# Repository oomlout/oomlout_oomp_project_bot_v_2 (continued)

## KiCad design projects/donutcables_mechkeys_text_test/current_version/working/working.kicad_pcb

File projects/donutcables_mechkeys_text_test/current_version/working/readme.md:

# mechkeys
 
## summary 
* id: donutcables_mechkeys_text_test
* user: donutcables
* name: mechkeys
* board: text_test
* repo: https://github.com/DonutCables/mechkeys
* src_file_repo_kicad_pcb: text-test-project/text-test.kicad_pcb
* src_file_repo_kicad_pcb_link: https://github.com/DonutCables/mechkeys/tree/master/text-test-project/text-test.kicad_pcb

* src_file_repo_sch: text-test-project/text-test.sch
* src_file_repo_sch_link: https://github.com/DonutCables/mechkeys/tree/master/text-test-project/text-test.sch
* full details link: https://github.com/oomlout/oomlout_oomp_project_bot_v_2/tree/main/projects/donutcables_mechkeys_text_test/current_version/working

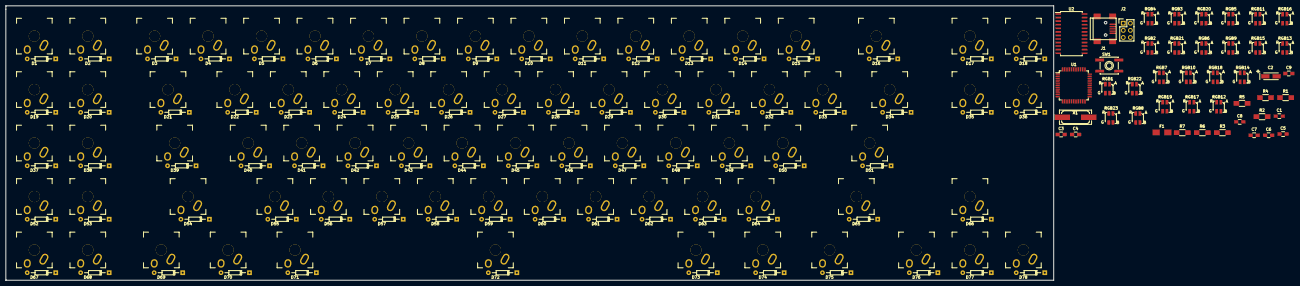
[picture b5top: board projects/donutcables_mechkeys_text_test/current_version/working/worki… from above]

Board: 2 copper layers, 373.4 x 97.8 mm, 202 parts (0 on the bottom side), 133 nets, no tracks yet.

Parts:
C1: C; C_0805_HandSoldering
C2: 10µF; TantalC_SizeA_EIA-3216_HandSoldering
C3, C4, C5, C9: 0.1µF; C_0805_HandSoldering
C6, C7: 18pF; C_0805_HandSoldering
C8: 1µF; C_0805_HandSoldering
D1, D2, D3, D4, D5, D6, D7, D8, D9, D10, D11, D12, D13, D14, D15, D16, D17, D18, D19, D20, D21, D22, D23, D24, D25, D26, D27, D28, D29, D30, D31, D32, D33, D34, D35, D36, D37, D38, D39, D40, D41, D42, D43, D44, D45, D46, D47, D48, D49, D50, D51, D52, D53, D54, D55, D56, D57, D58, D59, D60, D61, D62, D63, D64, D65, D66, D67, D68, D69, D70, D71, D72, D73, D74, D75, D76, D77, D78: D; Diode_DO-35_SOD27_Horizontal_RM10
F1: FP_Small; Fuse_SMD1206_HandSoldering
J1: USB_OTG; USB_Mini-B
J2: PRG; Pin_Header_Straight_2x03
R1: R; R_1206_HandSoldering
R2: R2; R_1206_HandSoldering
R3: R3; R_1206_HandSoldering
R4: R4; R_1206_HandSoldering
R5, R6: 22; R_1206_HandSoldering
R7: 10k; R_1206_HandSoldering
RGB1, RGB2, RGB3, RGB4, RGB5, RGB6, RGB7, RGB8, RGB9, RGB10, RGB11, RGB12, RGB13, RGB14, RGB15, RGB16, RGB17, RGB18, RGB19, RGB20, RGB21, RGB22, RGB23: Led_RGB_CA; SMP4-RGB
SW1: SW_RST; SW_SPST_EVQP0
SW_A_40: MX_LED; MXALPS-NOLED
SW_Alt_71, SW_Alt_73: MX_LED; MXALPS-NOLED
SW_B_59: MX_LED; MXALPS-NOLED
SW_Backspace_16: MX_LED; MXALPS-NOLED
SW_C_57: MX_LED; MXALPS-NOLED
SW_Caps_39: MX_LED; MXALPS-NOLED
SW_Ctrl_69: MX_LED; MXALPS-NOLED
SW_D_42: MX_LED; MXALPS-NOLED
SW_Del_35: MX_LED; MXALPS-NOLED
SW_E_24: MX_LED; MXALPS-NOLED
SW_Enter_51: MX_LED; MXALPS-NOLED
SW_F1_1, SW_F2_2, SW_F3_19, SW_F4_20, SW_F5_37, SW_F6_38, SW_F7_52, SW_F8_53, SW_F9_67, SW_F10_68: MX_LED; MXALPS-NOLED
SW_F_43: MX_LED; MXALPS-NOLED
SW_G_44: MX_LED; MXALPS-NOLED
SW_H_45: MX_LED; MXALPS-NOLED
SW_I_29: MX_LED; MXALPS-NOLED
SW_Ins_17: MX_LED; MXALPS-NOLED
SW_J_46: MX_LED; MXALPS-NOLED
SW_K_47: MX_LED; MXALPS-NOLED
SW_L_48: MX_LED; MXALPS-NOLED
SW_M_61: MX_LED; MXALPS-NOLED
SW_Menu_75: MX_LED; MXALPS-NOLED
SW_N_60: MX_LED; MXALPS-NOLED
SW_O_30: MX_LED; MXALPS-NOLED
SW_P_31: MX_LED; MXALPS-NOLED
SW_PgDn_36: MX_LED; MXALPS-NOLED
SW_PgUp_18: MX_LED; MXALPS-NOLED
SW_Q_22: MX_LED; MXALPS-NOLED
SW_R_25: MX_LED; MXALPS-NOLED
SW_S_41: MX_LED; MXALPS-NOLED
SW_Shift_54, SW_Shift_65: MX_LED; MXALPS-NOLED
SW_T_26: MX_LED; MXALPS-NOLED
SW_Tab_21: MX_LED; MXALPS-NOLED
SW_U_28: MX_LED; MXALPS-NOLED
SW_V_58: MX_LED; MXALPS-NOLED
SW_W_23: MX_LED; MXALPS-NOLED
SW_Win_70, SW_Win_74: MX_LED; MXALPS-NOLED
SW_X4Y1_3, SW_X5Y1_4, SW_X6Y1_5, SW_X7Y1_6, SW_X8Y1_7, SW_X8Y5_72, SW_X9Y1_8, SW_X10Y1_9, SW_X11Y1_10, SW_X12Y1_11, SW_X13Y1_12, SW_X13Y4_62, SW_X14Y1_13, SW_X14Y4_63, SW_X15Y1_14, SW_X15Y2_32, SW_X15Y3_49, SW_X15Y4_64, SW_X16Y1_15, SW_X16Y2_33, SW_X16Y3_50, SW_X17Y2_34, SW_X18Y5_76, SW_X19Y4_66, SW_X19Y5_77, SW_X20Y5_78: MX_LED; MXALPS-NOLED
SW_X_56: MX_LED; MXALPS-NOLED
SW_Y_27: MX_LED; MXALPS-NOLED
SW_Z_55: MX_LED; MXALPS-NOLED
U1: ATMEGA32U4RC-A; TQFP-44_10x10mm_Pitch0.8mm
U2: AN32183A; SOIC-24_7.5x15.4mm_Pitch1.27mm
X1: 16Mhz; Q_49U3HMS

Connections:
+5V: C2.1, C3.1, C4.1, C5.1, F1.2, J2.2, R7.2, RGB1.1, U1.2, U1.7, U1.14, U1.24, U1.34, U1.44
C1: SW_F1_1.SW1, SW_F3_19.SW1, SW_F5_37.SW1, SW_F7_52.SW1, SW_F9_67.SW1, SW_H_45.SW1, SW_Menu_75.SW1, SW_N_60.SW1, SW_X10Y1_9.SW1, SW_Y_27.SW1, U1.31
C2: SW_F2_2.SW1, SW_F4_20.SW1, SW_F6_38.SW1, SW_F8_53.SW1, SW_F10_68.SW1, SW_J_46.SW1, SW_M_61.SW1, SW_U_28.SW1, SW_X11Y1_10.SW1, SW_X18Y5_76.SW1, U1.32
C3: SW_Caps_39.SW1, SW_Ctrl_69.SW1, SW_I_29.SW1, SW_K_47.SW1, SW_Shift_54.SW1, SW_Tab_21.SW1, SW_X4Y1_3.SW1, SW_X12Y1_11.SW1, SW_X13Y4_62.SW1, SW_X19Y5_77.SW1
C4: SW_A_40.SW1, SW_L_48.SW1, SW_O_30.SW1, SW_Q_22.SW1, SW_Win_70.SW1, SW_X5Y1_4.SW1, SW_X13Y1_12.SW1, SW_X14Y4_63.SW1, SW_X20Y5_78.SW1, SW_Z_55.SW1
C5: SW_Alt_71.SW1, SW_Ins_17.SW1, SW_P_31.SW1, SW_S_41.SW1, SW_W_23.SW1, SW_X6Y1_5.SW1, SW_X14Y1_13.SW1, SW_X15Y3_49.SW1, SW_X15Y4_64.SW1, SW_X_56.SW1
C6: SW_C_57.SW1, SW_D_42.SW1, SW_E_24.SW1, SW_PgUp_18.SW1, SW_Shift_65.SW1, SW_X7Y1_6.SW1, SW_X8Y5_72.SW1, SW_X15Y1_14.SW1, SW_X15Y2_32.SW1, SW_X16Y3_50.SW1
C7: SW_Alt_73.SW1, SW_Del_35.SW1, SW_Enter_51.SW1, SW_F_43.SW1, SW_R_25.SW1, SW_V_58.SW1, SW_X8Y1_7.SW1, SW_X16Y1_15.SW1, SW_X16Y2_33.SW1, SW_X19Y4_66.SW1
C8: SW_B_59.SW1, SW_Backspace_16.SW1, SW_G_44.SW1, SW_PgDn_36.SW1, SW_T_26.SW1, SW_Win_74.SW1, SW_X9Y1_8.SW1, SW_X17Y2_34.SW1
D+: R6.1, U1.4
D-: R5.1, U1.3
GND: C1.2, C2.2, C3.2, C4.2, C5.2, C6.2, C7.2, C8.2, C9.2, J1.5, J1.6, J2.6, R1.2, SW1.1, U1.5, U1.15, U1.23, U1.33, U1.35, U1.43, U2.4, U2.9, U2.15, U2.23
LED_NSRT: U1.36, U2.22
LED_SCL: U1.18, U2.2
LED_SDA: U1.19, U2.3
unnamed: C1.1, U2.1, U2.13
unnamed: C6.1, U1.17, X1.1
unnamed: C7.1, U1.16, X1.2
unnamed: C8.1, U1.6
unnamed: C9.1, U1.42
unnamed: D1.2, SW_F1_1.SW2
unnamed: D2.2, SW_F2_2.SW2
unnamed: D3.2, SW_X4Y1_3.SW2
unnamed: D4.2, SW_X5Y1_4.SW2
unnamed: D5.2, SW_X6Y1_5.SW2
unnamed: D6.2, SW_X7Y1_6.SW2
unnamed: D7.2, SW_X8Y1_7.SW2
unnamed: D8.2, SW_X9Y1_8.SW2
unnamed: D9.2, SW_X10Y1_9.SW2
unnamed: D10.2, SW_X11Y1_10.SW2
unnamed: D11.2, SW_X12Y1_11.SW2
unnamed: D12.2, SW_X13Y1_12.SW2
unnamed: D13.2, SW_X14Y1_13.SW2
unnamed: D14.2, SW_X15Y1_14.SW2
unnamed: D15.2, SW_X16Y1_15.SW2
unnamed: D16.2, SW_Backspace_16.SW2
unnamed: D17.1, D18.1, D35.1, D36.1, D78.2, SW_X20Y5_78.SW2
unnamed: D17.2, SW_Ins_17.SW2
unnamed: D18.2, SW_PgUp_18.SW2
unnamed: D19.1, D20.1, D21.1, D22.1, D23.1, D24.1, D25.1, D26.1
unnamed: D19.2, SW_F3_19.SW2
unnamed: D20.2, SW_F4_20.SW2
unnamed: D21.2, SW_Tab_21.SW2
unnamed: D22.2, SW_Q_22.SW2
unnamed: D23.2, SW_W_23.SW2
unnamed: D24.2, SW_E_24.SW2
unnamed: D25.2, SW_R_25.SW2
unnamed: D26.2, SW_T_26.SW2
unnamed: D27.2, SW_Y_27.SW2
unnamed: D28.2, SW_U_28.SW2
unnamed: D29.2, SW_I_29.SW2
unnamed: D30.2, SW_O_30.SW2
unnamed: D31.2, SW_P_31.SW2
unnamed: D32.2, SW_X15Y2_32.SW2
unnamed: D33.2, SW_X16Y2_33.SW2
unnamed: D34.2, SW_X17Y2_34.SW2
unnamed: D35.2, SW_Del_35.SW2
unnamed: D36.2, SW_PgDn_36.SW2
unnamed: D37.1, D38.1, D39.1, D40.1, D41.1, D42.1, D43.1, D44.1
unnamed: D37.2, SW_F5_37.SW2
unnamed: D38.2, SW_F6_38.SW2
unnamed: D39.2, SW_Caps_39.SW2
unnamed: D40.2, SW_A_40.SW2
unnamed: D41.2, SW_S_41.SW2
unnamed: D42.2, SW_D_42.SW2
unnamed: D43.2, SW_F_43.SW2
unnamed: D44.2, SW_G_44.SW2
unnamed: D45.2, SW_H_45.SW2
unnamed: D46.2, SW_J_46.SW2
unnamed: D47.2, SW_K_47.SW2
unnamed: D48.2, SW_L_48.SW2
unnamed: D49.2, SW_X15Y3_49.SW2
unnamed: D50.2, SW_X16Y3_50.SW2
unnamed: D51.2, SW_Enter_51.SW2
unnamed: D52.1, D53.1, D54.1, D55.1, D56.1, D57.1, D58.1, D59.1
unnamed: D52.2, SW_F7_52.SW2
unnamed: D53.2, SW_F8_53.SW2
unnamed: D54.2, SW_Shift_54.SW2
unnamed: D55.2, SW_Z_55.SW2
unnamed: D56.2, SW_X_56.SW2
unnamed: D57.2, SW_C_57.SW2
unnamed: D58.2, SW_V_58.SW2
unnamed: D59.2, SW_B_59.SW2
unnamed: D60.2, SW_N_60.SW2
unnamed: D61.2, SW_M_61.SW2
unnamed: D62.2, SW_X13Y4_62.SW2
unnamed: D63.2, SW_X14Y4_63.SW2
unnamed: D64.2, SW_X15Y4_64.SW2
unnamed: D65.2, SW_Shift_65.SW2
unnamed: D66.2, SW_X19Y4_66.SW2
unnamed: D67.2, SW_F9_67.SW2
unnamed: D68.2, SW_F10_68.SW2
unnamed: D69.2, SW_Ctrl_69.SW2
unnamed: D70.2, SW_Win_70.SW2
unnamed: D71.2, SW_Alt_71.SW2
unnamed: D72.2, SW_X8Y5_72.SW2
unnamed: D73.2, SW_Alt_73.SW2
unnamed: D74.2, SW_Win_74.SW2
unnamed: D75.2, SW_Menu_75.SW2
unnamed: D76.2, SW_X18Y5_76.SW2
unnamed: D77.2, SW_X19Y5_77.SW2
unnamed: F1.1, J1.1
unnamed: J1.2, R5.2
unnamed: J1.3, R6.2
unnamed: R1.1, U2.24
unnamed: R2.1, RGB1.4
unnamed: R3.1, RGB1.3
unnamed: R4.1, RGB1.2
unnamed: U2.7, U2.17
PWM_BLUE: R2.2, U1.12
PWM_GREEN: R3.2, U1.30
PWM_RED: R4.2, U1.29
R1: D1.1, D2.1, D3.1, D4.1, D5.1, D6.1, D7.1, D8.1, U1.8
R2/SCK: J2.3, U1.9
R3/MOSI: J2.4, U1.10
R4/MISO: J2.1, U1.11
R5: D67.1, D68.1, D69.1, D70.1, D71.1, D72.1, D73.1, D74.1, U1.28
R6: D9.1, D10.1, D11.1, D12.1, D13.1, D14.1, D15.1, D16.1, U1.41
R7: D27.1, D28.1, D29.1, D30.1, D31.1, D32.1, D33.1, D34.1, U1.40
R8: D45.1, D46.1, D47.1, D48.1, D49.1, D50.1, D51.1, U1.39
R9: D60.1, D61.1, D62.1, D63.1, D64.1, D65.1, D66.1, U1.38
R10: D75.1, D76.1, D77.1, D78.1, U1.37
RST: J2.5, R7.1, SW1.2, U1.13
Z1: RGB2.3, RGB3.1, RGB5.1, RGB13.1, RGB22.3, RGB23.3, U2.19
Z2: RGB2.2, RGB3.2, RGB6.1, RGB9.2, RGB10.2, RGB11.2, RGB12.2, RGB14.1, U2.18
Z3: RGB2.1, RGB3.3, RGB7.1, RGB9.3, RGB10.3, RGB11.3, RGB12.3, RGB15.1, U2.16
Z4: RGB2.4, RGB3.4, RGB4.4, RGB8.1, RGB9.4, RGB10.4, RGB11.4, RGB12.4, RGB16.1, U2.14
Z5: RGB4.2, RGB5.2, RGB6.2, RGB7.2, RGB8.2, RGB9.1, RGB17.1, RGB20.2, RGB21.2, RGB22.2, U2.12
Z6: RGB4.3, RGB5.3, RGB6.3, RGB7.3, RGB8.3, RGB10.1, RGB18.1, RGB20.3, RGB21.3, RGB22.1, U2.11
Z7: RGB4.1, RGB5.4, RGB6.4, RGB7.4, RGB8.4, RGB19.1, RGB20.4, RGB21.4, RGB22.4, U2.10
Z8: RGB11.1, RGB13.2, RGB14.2, RGB15.2, RGB16.2, RGB17.2, RGB18.2, RGB19.2, RGB20.1, RGB23.2, U2.8
Z9: RGB12.1, RGB13.3, RGB14.3, RGB15.3, RGB16.3, RGB17.3, RGB18.3, RGB19.3, RGB21.1, RGB23.1, U2.6
Z10: RGB13.4, RGB14.4, RGB15.4, RGB16.4, RGB17.4, RGB19.4, RGB23.4, U2.5

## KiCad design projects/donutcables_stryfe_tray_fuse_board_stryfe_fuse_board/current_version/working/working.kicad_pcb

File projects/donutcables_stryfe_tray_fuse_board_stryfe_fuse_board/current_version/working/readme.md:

# stryfe_tray_fuse_board
 
## summary 
* id: donutcables_stryfe_tray_fuse_board_stryfe_fuse_board
* user: donutcables
* name: stryfe_tray_fuse_board
* board: stryfe_fuse_board
* repo: https://github.com/DonutCables/Stryfe_Tray_Fuse_Board
* src_file_repo_kicad_pcb: stryfe_fuse_board.kicad_pcb
* src_file_repo_kicad_pcb_link: https://github.com/DonutCables/Stryfe_Tray_Fuse_Board/tree/main/stryfe_fuse_board.kicad_pcb
* src_file_repo_kicad_sch: stryfe_fuse_board.kicad_sch
* src_file_repo_kicad_sch_link: https://github.com/DonutCables/Stryfe_Tray_Fuse_Board/tree/main/stryfe_fuse_board.kicad_sch

* src_file_repo_sch: 
* src_file_repo_sch_link: https://github.com/DonutCables/Stryfe_Tray_Fuse_Board/tree/main/
* full details link: https://github.com/oomlout/oomlout_oomp_project_bot_v_2/tree/main/projects/donutcables_stryfe_tray_fuse_board_stryfe_fuse_board/current_version/working

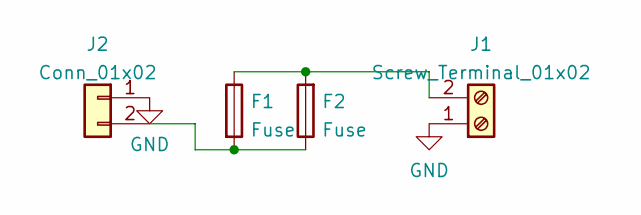
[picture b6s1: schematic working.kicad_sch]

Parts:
F1: Fuse; Fuseholder_Blade_ATO_Littelfuse_Pudenz_2_Pin
F2: Fuse; Fuseholder_Blade_Mini_Keystone_3568
J1: Screw_Terminal_01x02; Amass_XT60PW-M_Kombifootprint
J2: Conn_01x02; Amass_XT60PW-M_Kombifootprint

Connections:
GND: J1.1, J2.1
unnamed: F1.2, F2.1, J2.2
unnamed: F1.1, F2.2, J1.2

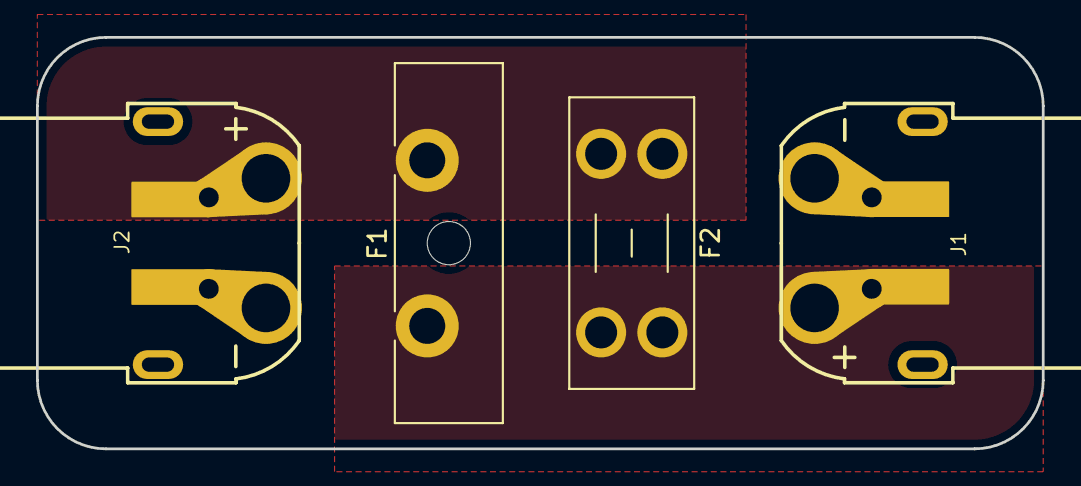
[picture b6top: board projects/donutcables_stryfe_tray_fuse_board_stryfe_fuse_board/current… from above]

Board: 2 copper layers, 55.9 x 22.9 mm, 4 parts (0 on the bottom side), 3 nets.
